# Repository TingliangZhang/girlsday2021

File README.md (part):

# Girl's Day of 2021 Presents Design
2021年交叉班女生节礼物——名片 设计

智能名片交互hhh

赛博朋克区块链

## 功能

Tagmo - 制作自己的Amiibo

[Popl - Your digital business card](https://popl.co/)

卡里面只有一个ID和我们服务器网址信息，具体这张名片能传达多少社交信息就由用户在网页端或者客户端配置了。以及最好加密一下，防止被轻易拿去干别的，比如友商出个教程，我们的卡就都变成他们的了

[The Blue Smart Card](https://blue.social/) - Reinventing the Name Tag. Create your virtual identity and be social again.

[Mobilo - The Smart Business Card](https://www.mobilocard.com/)

[Fuze Card, 0.84mm innovative electronic card technology.](https://fuzecard.com/)

KickStarter页面 [Fuze Card](https://www.indiegogo.com/projects/fuze-card-your-whole-wallet-in-one-card--3#/): Your Whole Wallet in One Card

[Unbox Therapy](https://www.youtube.com/channel/UCsTcErHg8oDvUnTzoqsYeNw)评测视频：[Your Whole Wallet In One Card](https://www.youtube.com/watch?v=7SPOVJi3H6g)

[Find Your Keys, Wallet & Phone with Tile's App and Bluetooth](https://www.thetileapp.com/en-us/)

[2.13寸 无源NFC 墨水屏 e-paper ESL电子货架标签 无线供电/刷新](https://item.taobao.com/item.htm?id=613699970326)

微雪NFC墨水屏标签

[小米碰碰贴2](https://item.jd.com/100014996634.html) nfc感应开关 全能投屏音乐接力碰触连网一碰连接米家智能场景

## 可参考项目

[PCB Business Card With NFC](https://www.instructables.com/PCB-Business-Card-With-NFC/) - 能存网址的名片

[THE NFC KEY](https://n-o-d-e.net/nfckey.html) - 存储密钥的带物理按键NFC

[Digital Business Card With NFC](https://www.instructables.com/Digital-Business-Card-With-NFC/) - 只是把NFCTag扔进两张纸之间去了。

[StyloCard](https://mitxela.com/projects/stylocard) - 乐器名片

[L-ink_Card](https://github.com/peng-zhihui/L-ink_Card) - 带墨水屏的NFC Tag

## 问题

手机的NFC功能可能默认关闭，而且NFC线圈位置不固定：苹果在正面顶部，安卓手机大多在背面。

## 进度追踪

2020/12 提出想法，女生节送智能名片

2021/1/27 开始设计

2021/1/28-29 元件选型和天线参数计算

2021/1/30-2/2 天线python脚本生成编写

2021/2/2 第一版测试板交付嘉立创打样，同时采购了元件，同时着手买NFC和RFID读取器

2021/2/4 V2交付打样，使用白色阻焊，尝试效果

2021/2/7 V1V2打样完成，焊接测试完成，功能完好

2021/2/8 开始规划网站服务，并学习React框架

2021/2/9 M24LR-discovery到货，验证了M24能用3.3V驱动STM32L系列单片机和一个液晶数位屏

2021/2/10 诚驰大哥加入，换用VUE框架，小菜鸡我同步开始学Vue

2021/2/11 除夕，依然干活，微雪的2.7inch NFC e-paper到货，测试尝试复现，并用电纸屏送上新年祝福

2021/2/12 大年初一，选取UX和UI设计工具，开始学习Figma

2021/2/13 开工画UX，画了一上午画出来一个登录界面，UX设计师真不容易，决定先用iPad的Procreate来画草图。

2021/2/15 用户体验设计碰头会，根据建议大改了交互流程，继续画了卡片管理界面，同时注册域名

2021/2/16 交给诚驰写网站，开始头大的Ruby和Jekyll开发环境配置

2021/2/17 搞网站备案，头大，Ruby和Jekyll开发环境还是没配好

2021/2/18 为了拿备案服务号，购买了阿里云一年的主机，并且配置Ubuntu环境和VS Code网页版，终于提交管局审核。把一大箱硬件开发的东西寄回清华。

2021/2/19 把Ruby和Jekyll开发环境配置好，其实就放弃了动态构建，只用build吧，研究Jekyll主题的使用

2021/2/20 返校，使用Ubuntu环境跑Jekyll

2021/2/21 - 22 组装服务器并给服务器装系统，走了很多弯路

2021/2/23 装好了Debian KDE 图形化系统，开始探索如何装虚拟化环境、网站部署

2021/2/24 开始部署Proxmox VE虚拟化服务，遇到了网关和DNS一系列问题

2021/2/25 两网站备案成功，但是服务器还是没跑起来，考虑回退回Debian Buster单系统，继续部署网站。

2021/2/26 开始第二个版本的PCB，准备采用黑色Silkskin，银色Paste，背面参考PCB尺子的设计。同时写社交模式。

2021年2月26日22点前后，人生中第一台自己搭出来的服务器和虚拟化子系统开始运行，快乐！

2021/2/27 确定正反面的形式，找到PCB Ruler参考

2021/2/28 传媒研究，定义碰一碰陌生人社交

2021/3/1 绘制V3样板

2021/3/2 交付打样，一共18个订单

2021/3/3 - 3/7 等待到货，同时在阿里云上部署服务，已部署主页和博客俩服务

2021/3/8 在女生节后一天，卡片到货了总共用了一周，嘉立创产能emmm。开始写文档梳理整件事情

2021/3/9 - 10 继续写

2021/3/11-12 要做发布会视频，24h速成blender

2021/3/13 焊芯片+做发布会PPT+建模

## To Do List

- [x] 云服务器配置
- [x] 本地服务器搭建（Dell R720）
- [x] 域名注册
- [x] 域名备案
- [x] SSL证书（上https）
- [x] 网站搭建
- [x] PCB外观设计
- [x] 自动生成PCB脚本编写（集成bitmap2component）
- [x] 硬件原理调试
- [x] UX和UI设计
- [x] 用户体验测试（大雾）
- [x] SD卡大小Tag设计和测试，特别是V槽拼版
- [ ] 加入墨水屏

## 工具

[KiCAD](http://www.kicad.org/)及其插件

[Interactive HTML BOM plugin for KiCad](https://github.com/openscopeproject/InteractiveHtmlBom)

[AutoCAD](https://www.autodesk.com/products/autocad/overview) 2021 Edu Edition

Linux下软件：

[Krita | Digital Painting. Creative Freedom.](https://krita.org/) 绘画软件

[Draw Freely | Inkscape](https://inkscape.org/) 矢量图编辑器

## 外形设计Outline

依据身份证等使用的ISO 7810-2003国际标准中的ID-1：ID-1的规定尺寸为85.60×53.98毫米（3.370×2.125英寸），常用于身份证、银行卡（如提款卡、信用卡）、驾照、个人名片，以及商店发出的忠实顾客卡等。其长宽比与黄金分割（1.618:1）接近。

ISO 7813规范ID-1塑胶银行卡的附加特性，包括0.76毫米厚度，及3.18毫米半径的圆角。

所以设计为

85.60×53.98毫米

3.18毫米半径的圆角

0.76毫米厚度（做0.8mmPCB板）

横向排版

或者用ID-3画成小的钥匙链

## Tile大小版本设计

Tile Pro：42mm x 42mm x 6.5mm  孔7mm直径

Tile Mate：35mm x 35mm x 6.2mm 孔6.5mm

初步设计为 40mm x 40mm x 1.6mm 孔6mm直径 倒角5mm直径圆

天线尺寸为30x30mm 0.3x0.3mm 11圈，电感4.98uH(@13.56Mhz)

天线封装焊盘为 0.3 x 0.5mm圆形通孔（嘉立创双面板最小过孔内径0.3mm,最小外径0.5mm）和 0.3 x 0.5mm矩形贴片焊盘

[嘉立创教学系列之：各软件拼板作业指引](http://club.szlcsc.com/article/details_468_1.html)

嘉立创拼版V割出货：走线和焊盘距板边距离≥0.4mm，否则可能涉及到板内的线路及焊盘，如果是拼版，则线离边必须要有0.4mm间距，否则v割会伤到线路。如果是单片出货，则需要帮≥0.2mm的间距。

VCUT(V割)板边离线的距离不小于0.4MM，CNC（锣边）正常是版边离线的距离不小于0.3MM，内槽离走线离线的最小距离不得小于0.3MM

V-CUT（V割工艺）：

（1）V割的拼板，板与板相连处不留间隙，也就是两块板外形线重叠放置，但是要注意，板子内的导线离V割线距离不小于0.4mm，以免切割时伤到走线。

（2）一般V割后残留的深度为1/3板厚，产品手动掰开后由于玻璃纤维丝有被拉松的现象，尺寸会略有超差，个别产品会偏大以上。

（3）V-CUT刀只能走直线，不能走曲线和折线。

（4）拼板尺寸在8cm以上才能做V-CUT工艺。

拼版设计：

可以考虑30cm x 30cm 九块边缘倒角板子拼起来，横排中间留2mm锣边，纵排无间距V割，纵排两侧有5mm工艺边和2.0mm定位孔及1.0mm的Mark点（一个焊盘）。

全部画在EdgeCut里面就好，嘉立创OEM会帮忙加V割或者锣边，如果版式一样，可以只画一个电路。在复制EdgeCut层的时候，可以在右边隐藏别的层。

由于强度问题，拼版V割的话还是要紧密连接，不能像上面这种设计。必须要加支撑才行。

但是拼版订单要多加钱。

所以还是先打单板吧。

## 简笔画头像生成

CV算法生成简笔画头像

[ArtLine](https://github.com/vijishmadhavan/ArtLine)

运行环境：[Colab](https://colab.research.google.com/github/vijishmadhavan/Light-Up/blob/master/ArtLine.ipynb)

CoLab中图片拖到根目录去上传，之后导入：

```python
img = PIL.Image.open("cai.jpg").convert("RGB")
```

[U-2-Net](https://github.com/NathanUA/U-2-Net)还有其前身[APDrawingGAN](https://github.com/yiranran/APDrawingGAN)

## 芯片选型

NXP NTAG

https://www.themobileknowledge.com/wp-content/uploads/2018/07/02-Webinar-slies-Antenna-design-for-NTAG-I2C-plus.pdf

ST25 Dynamic NFC Tags

https://www.st.com/en/nfc/st25-dynamic-nfc-tags.html

ST25DV04K

https://www.st.com/en/nfc/m24lr04e-r.html#overview

[M24LR04E-RMN6T/2](https://item.szlcsc.com/168717.html)[射频卡芯片](https://list.szlcsc.com/catalog/981.html)

测试板：

[M24LR-DISCOVERY](https://www.st.com/en/evaluation-tools/m24lr-discovery.html)

[X-NUCLEO-NFC02A1](https://www.st.com/en/ecosystems/x-nucleo-nfc02a1.html)

## NFC线圈设计

NFC Antenna Generator

https://kbeckmann.github.io/2016/06/19/NFC-Antenna-Generator/

[NFC Antenna Design | RF Design | eDesignSuite](https://eds.st.com/antenna/)

电路中天线电感计算计算：

主要参考AN2866 -  Antenna design procedure

Internal tuning capacitor in ST25DV04K SO8N(f = 13.56 MHz) $C_{TUN} = 28.5 pF$

计算公式：
$$
L_{A} C_{S} \omega^{2}=1
$$
具体推导：
$$
L_{A}=\frac{1}{4 \pi^{2} f^{2} C_{S}}
$$

$$
L_{A}=\frac{1}{4*3.14^{2}*13.56^{2}*28.5}=4.84uH
$$

谐振理论：

At low frequencies $\left(f<f_{\text {self res }} / 10\right),$ the stray capacitance $C_{\text {ant }}$ is negligible, $L_{A}=L_{\text {ant }}$ and the antenna reactance is given by $X_{A}=j L_{\text {ant }} \omega$.
At $13.56 \mathrm{MHz}, \mathrm{C}_{\text {ant }}$ value gets in the range of some $\mathrm{pF}$ and $\mathrm{L}_{\mathrm{A}}>\mathrm{L}_{\text {ant }}$.

The antenna impedance is $Z_{\text {ant }}=R_{A}+j L_{A} \omega$.

The NFC / RFID chip impedance is $Z_{S}=R_{s}+j / C_{S} \omega$.

For the equivalent RLC circuit, the total impedance is $Z_{\text {tot }}=Z_{\text {ant }}+Z_{s}$ and the resonant frequency is given by the condition $L_{A} C_{S} \omega^{2}=1$.
Optimum antenna tuning

At resonant frequency the total impedance reaches its minimum value $Z_{\text {tot }}=R_{A}+R_{S}$. The current in the antenna and the voltage delivered to the NFC / RFID chip are maximized, as the energy transferred to the device.

物理天线电感

嘉立创PCB成品外层铜厚1oz~2oz(35um~70um)选择35um

单片出货，走线和焊盘距板边距离≥0.2mm，否则可能涉及到板内的线路及焊盘。

直接留3.18mm边缘。

最小线隙，多层板3.5mil 单双面板5mil (1mil=1/1000inch=0.0254mm)

Antenna Length =  85.60 - 3.18x2 = 79.24 mm

Antenna Width = 53.98 - 3.18x2 = 47.62 mm

Turns = 6

Equivalent Inductance@13.56 Mhz = 4.98 µH

考虑到布线过程中的寄生电容等，接近4.84 µH，可以接受这一设计。

动态NFC天线计算主要参考 AN2972 How to design an antenna for dynamic NFC tags 

封装库画六圈螺线太难了，准备用dxf导入，先使用Adobe Illustrate绘制，依然太麻烦放弃。

还是写py脚本向导吧。

## NFC Antenna创建向导编写

参考官方示例

https://docs.kicad.org/5.1/en/pcbnew/pcbnew.html#Footprint_Wizards

[KiCad Scripting Examples](https://kicad.mmccoo.com/?page_id=83)

参考C:\Program Files\KiCad\share\kicad\scripting\plugins中的脚本。

C:\Users\Zhang\AppData\Roaming\kicad\scripting\plugins

[KiCad](https://github.com/KiCad)/**[kicad-footprint-wizards](https://github.com/KiCad/kicad-footprint-wizards)**

Defining Parameters

Footprint wizards are written in Python and are simple to develop. Each footprint wizard defines a number of footprint parameters, which are organised into categories called "Pages". [Read further on footprint parameters](https://github.com/KiCad/Footprint_Wizards/wiki/Footprint-Parameters)

主要参考microMatch_connectors.py，焊盘直接用SMD的长方形焊盘

To greatly simplify development of custom footprint wizards, the FootprintWizard base class is provided, and only a handful of simple functions need to be written for each wizards. [Read further on minimum wizard requirements](https://github.com/KiCad/Footprint_Wizards/wiki/Minimum-Wizard-Requirements)

先画一个最简单的练手

注意每次更改需要重启KiCAD新脚本才能生效，DeBug的时候因为这个浪费了不少时间。如果加载脚本失败，可以看到报错信息。

通过self.AddParam("Conductor", "spacing", self.uMM, 0.6)传递进来的 self.uMM 其实是已经转化成nm为单位的整型变量了，不需要再用pcbnew.FromMM(1.0)转换为nm。

算法可参考HTML的脚本，but我选择自己写hhh

二维数组需要初始化，测试py文件单独编写测试，VScode在安装Python插件后可以在Debug标签页查看变量。

之后手动添加焊盘，嘉立创双面板最小过孔内径0.3mm,最小外径0.5mm，一号焊盘用0.6x1.524mm矩形贴片，注意取消勾选F.Paste和F.Mask工艺层以令外观美观，二号焊盘用圆形通孔0.8x0.5mm，注意取消勾选F.Mask和B.Mask工艺层以令外观美观

左下角：（100，100）

右上角：（185.6，46.02）

中心定位点：（142.8，73.01）

## 信息填写

QR Code Wizard使用丝印层而非铜层

> Use SilkS layer: True
> Use Cu layer: False

字符：

最小字符：线宽6mil 字符高40mil，参数为极限值，尽量大于此参数

故字符采用0.2mm线宽 1mm字符高度

目前仅支持英文字符，KiCAD 6.0 将支持中文字符输入

## 矢量图导入

使用KiCAD主页 位图转换为元件 工具进行转换，直接可以导出kicad_mod文件，注意选择顶层丝印。

调黑白阈值还是很丑的，可以考虑通过Artline生成简笔画。

调整尺寸需要通过调分辨率实现，DPI越高图片越小。注意名片尺寸为85.60×53.98毫米，合适的头像应当为30mm x 30mm

同学们的头像参数调节

| Who      | DPI  | 尺寸      | 黑白阈值 |
| -------- | ---- | --------- | -------- |
| NFC Logo | 4000 | 10 x 10mm | 30       |
| cai      | 600  | 26 x 26mm | 80       |
| luna     | 700  | 30 x 30mm | 70       |
| danni    | 300  | 37.3      | 30       |

[Artistic PCB Design for Terrified Beginners](https://wiki.hope.net/index.php?title=Artistic_PCB_Design_for_Terrified_Beginners_workshop)

## NFC + 墨水屏

[实用新型] 一种无源NFC电子墨水屏显示系统 申请号：2020204091829

微雪e-Paper相关资料

https://www.waveshare.net/wiki/Main_Page#Display-e-Paper

特别是驱动板如[e-Paper Driver HAT](https://www.waveshare.net/wiki/E-Paper_Driver_HAT)等

但是屏线多数是SPI，所以估计需要一个STM32转接一下，其实之后的按键等外围设备也需要一个单片机来做。

NFC墨水屏模块

https://www.waveshare.net/wiki/2.7inch_NFC-Powered_e-Paper_Module

NFC烧写器开发板

https://www.waveshare.net/wiki/ST25R3911B_NFC_Board

购买了以上两种产品，发现NFC墨水屏的主控芯片型号竟然被磨掉了。。。

通过SWD接口接入，读取到型号是[STM32L4P5/Q5](https://www.st.com/en/microcontrollers-microprocessors/stm32l4p5-q5.html)，不出所料，ultra‐low‐power系列。

旁边的那个写着ofz 02f s20x的6pin芯片是 TPS62122，降压dcdc

NFC Tag估计是用STM32搞的，用NFC Tools Pro读取得到型号，是一个NXP MIFARE Ultralight

现在量一下电容充电曲线，7.5V，在识别和写图的时候充能，但是没有明显的充放电，应该就是个小电容。

## V1V2焊接调试

注意ST24的marker是一边的斜边对应1号脚所在的位置，其实反色的ST标着对应的也是marker。

在不带载的情况下，EH输出大约为0.5V以下。暂时不上LED了，LED允许电压普遍在2.5V 20mA左右，可能会BOOM。下个版本加电阻吧。

## V3名片设计

增加LED限流电阻

在背面增加两个具有代表性的SMD芯片封装，贴片装饰LQFP-100和BGA-1mm-256

删除头像丝印，规范个人信息排版方式

删除中心定位焊盘

### V3.0 被抛弃的花里胡哨的PCB信仰尺风格设计

背面参考PCB尺子的设计

最典型的就是NVIDIA的尺子，但是可能找不到源文件，只能找类似的参考。

嘉立创PCB

https://lceda.cn/OSHWHubkai-yuan-ying-jian/li-chuangeda-chi-zi

Github and KiCAD

[PCBruler Github Repo](https://github.com/jbtronics/PCBruler)  [PCBrulerS Project Intro](https://hackaday.io/project/25482-pcbrulers) 准备主要参考这一个

[PCB Business Card Ruler With QR and NFC](https://www.instructables.com/PCB-Business-Card-Ruler-With-QR-and-NFC/)

Eagle 开源

[Adafruit-PCB-Ruler](https://github.com/adafruit/Adafruit-PCB-Ruler)

[SparkFun_PCB_Ruler](https://github.com/sparkfun/SparkFun_PCB_Ruler)

放张图纪念一下一晚上的工作

### V3.1版本 简约风设计

考虑电路在背面，个人信息在正面。

背面增加未来交互Logo，在铜层，加阻焊，闪闪发光其实不好看

25mm x 25mm 大小

有一个问题，Logo存在闭合曲线部分，可能电磁感应会有问题，特别是有一部分特别细，有冒烟隐患。

需要更改文件，切断最细部分的连线。由于没有Ai，我用画图3D加上了两个白色的直角三角形，从而断开了回路。

同时删除中心定位焊盘，加入辅助轴原点。

名片正面信息：

姓名

个人标签，如：

交互设计师，用户体验工程师，网页前端架构师，艺术家，嵌入式工程师

美术农民工，影视包工头，码农，极客

头像：30x30mm大小，线宽至少0.2mm

缩放按照1500DPI来，线宽能达到0.3mm，34.7mm正方形，有点大，得调整位置。

身份信息：

Tsinghua University

Info Art Design

Interdisciplinary Project ?

UID?

二维码决定先不做定制化，统一写为interact.cool网址，即跳转到网站登录或APP下载页面，登陆后双方互扫UID码即可。

Designed by Tingliang, Copyright © 2021 Tingliang Zhang CC BY-NC-ND

## V4钥匙链设计

缩小钥匙孔、线圈、整个的尺寸，到30x30cm，以便一个10x10的上面能打9个。

在正面印上未来交互的图案，背面印上二维码。和部分装饰性丝印，比如LQFP-64和BGA-100

天线重新生成一下：0.3mm线宽、0.2mm间距、25*25mm、13圈的线圈，自感4.97uH，接近4.84uH

0.8mm板厚，选择白色或黑色阻焊，3x3V-Cut拼板

## 服务器搭建

服务器选型

Dell R720 2U刀片服务器 3.5寸盘架x8  双路至强E5-2678V2 20核40线程处理器 16G内存 H710阵列卡 3T储存空间（后续可扩容） 750W电源 100Mbps带宽 公网IP

最好带有DELL IDRAC7 企业版授权

BUT 校内1024以下端口不开，而且会被学校查水表，不让校内建站。所以可能还是学生机更好。。。

使用阿里云学生机吧。。。

三丰云可以免费用，但是只用作测试，不能用为生产环境，因为每五天需要点一次延期，太过分了。

[PowerEdge R720](https://www.dell.com/support/home/zh-cn/product-support/product/poweredge-r720/overview)

服务编号(Service Tag)：C8L4Z42

操作系统选择Debian+KVM(Ubuntu+WinServer)

插上E5-2680v2，内存条，开机

第一次开机先清一下H710的默认值，可能之前的设置不对。

重启后按F2进入System Config，最后发现是盘没插好，2.5寸用3.5寸盘架还是有点问题，换成3.5寸就好了

F2-System Setup - Device Settings - H710 Raid setting - Create new virtual disk - Save and restart   就可以成功挂在硬盘到阵列卡上面了，当有 1 Virtual Device 的时候就说明成了。

但是又识别不到U盘了，可能是因为有阵列卡？也可能没断电插拔？重新烧写后按F10-BOOT setting 选择USB设备启动。

注意Debian Live KDE的安装界面锁屏默认密码为Live

总结：首先F2-System Setting - Device Setting - H710 - Create new virtual disk - Initialize - Fast Initialize 

替代办法：https://jingyan.baidu.com/article/4b52d702b7d396fc5d774b49.html 直接ctrl + R进入Raid设置

在BIOS Setting 确认SATA setting是Raid

重启，没有直接引导，需要按F11选择C：-- USB 启动即可

安装的时候BUG无法分区...搜了一下，是因为2T+硬盘要切换成UEFI

[Dell R720上的系统安装问题的解决办法](https://www.cnblogs.com/wgp13x/p/3750957.html)

可以使用[Microsoft Windows and Office ISO Download Tool](https://www.heidoc.net/joomla/technology-science/microsoft/67-microsoft-windows-and-office-iso-download-tool)下载Windows系统，但是好像没有Windows Server 2019

先安Debian：[Debian 64 位 PC（amd64）的安装手册](https://www.debian.org/releases/stable/amd64/)

去tuna下载[Debian 10.8.0 (amd64, DVD installer (Part 1))](https://mirrors.tuna.tsinghua.edu.cn/debian-cd/current/amd64/iso-dvd/debian-10.8.0-amd64-DVD-1.iso)

先安Ubuntu吧qwq

[Installation instructions for Ubuntu Server ](https://ubuntu.com/tutorials/tutorial-install-ubuntu-server)

按照[Create a bootable USB stick on Windows](https://ubuntu.com/tutorials/create-a-usb-stick-on-windows)使用[Rufus](https://rufus.ie/)烧写U盘

最后还是决定用Debian了。。。在Debian里在搞虚拟化主机KVM安Windows之类的

TFTP网络配置需要认真看看。

操作系统选择方面，先使用VirtualBox尝试安装，比如Debian Live之类的。

Debian的各种桌面环境参考：https://www.eet-china.com/mp/a10976.html

[Debian 10.8.0 (amd64, Live CD with gnome and non-free firmware)](https://mirrors.tuna.tsinghua.edu.cn/debian-nonfree/images-including-firmware/current-live/amd64/iso-hybrid/debian-live-10.8.0-amd64-gnome+nonfree.iso)

总结如下：

1. 建立Raid
- 开机，按ctrl+R进行Raid配置
- 选择Raid卡，按F2，清除现有Raid
- 光标选择到Raid卡，按F2，create new VD，将6个HD全做Raid5（或Raid6）
- 按F2，init VD （初始化VD）
- 配置完成后重启
2. 开机按F2进行BIOS设置 （如果总硬盘小于2T此步略去）进入BIOS，将启动模式选择成UEFI
3. 开机按F11进行UEFI启动（如果总硬盘小于2T此步略去）
4. 进入Boot Manager，选择UEFI Boot Menu（如果总硬盘小于2T，选择Bios Boot Menu）
5. 选光驱（插入系统盘）
6. Press any key to install OS

后续高分屏问题解决：尝试使用Quadro K2200专业卡，使用DP输出，但是后面板挡住了DP线，需要一个扁平一点的DP。

服务器后台运行在后面加 & 即可

如果有输出，ssh断开后程序也可能会停止运行，所以在前面加上 nohup

Debian10第一次安装ssh：

```bash
sudo apt-get install ssh
sudo systemctl restart ssh
```

之后可以配置公钥

## 域名备案相关

总的来说：麻烦到爆炸

在购买域名的代理商处进行域名实名认证，在购买云服务器的运营商拿备案服务号，并走备案网站流程。

首先域名实名认证，三天后同步到管局，进行网站备案

在阿里[备案入口](https://beian.aliyun.com/)上传一大堆资料和无数次验证码之后，提交初审，一个工作日后会给你打电话确认，把你的资料改一遍，个人申请不能涉及团队，之后提交管局。

工信部会给你发个短信再次查验身份。

阿里云管局审核最快也得一周以后，基本上通过都是两周以后

备案成功后，会给你的手机，邮箱发送一个备案密码，以及备案号，备案密码一定要好好保管，备案密码是以后变更备案信息的重要依据。

我今天（2021年2月18日）提交的管局审核，女生节前希望能批下来。

## 阿里云服务器相关

纠结好久，最后选择购买阿里云的[轻量应用服务器](https://www.aliyun.com/product/swas)，首先有学生价，其次可以安装Ubuntu，比腾讯云的轻量应用服务器要好。

最主要的是，[网站备案](https://beian.aliyun.com/)需要的[备案服务号](https://help.aliyun.com/document_detail/36938.html)轻量应用服务器实例可以提供5个（参见[支持备案的云服务及备案网站数量](https://help.aliyun.com/document_detail/36891.html)）

我选择安装Ubuntu20.04，进去之后好快啊，通过输入“sudo su root”切换至root账号

可选[用VNC搭建Ubuntu VNC可视化界面](https://help.aliyun.com/knowledge_detail/59330.html)

vnc4server还没出Ubuntu20.04版本的，啊这。。。

我还是用[code-server](https://github.com/cdr/code-server)吧。

### Code-Server安装

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
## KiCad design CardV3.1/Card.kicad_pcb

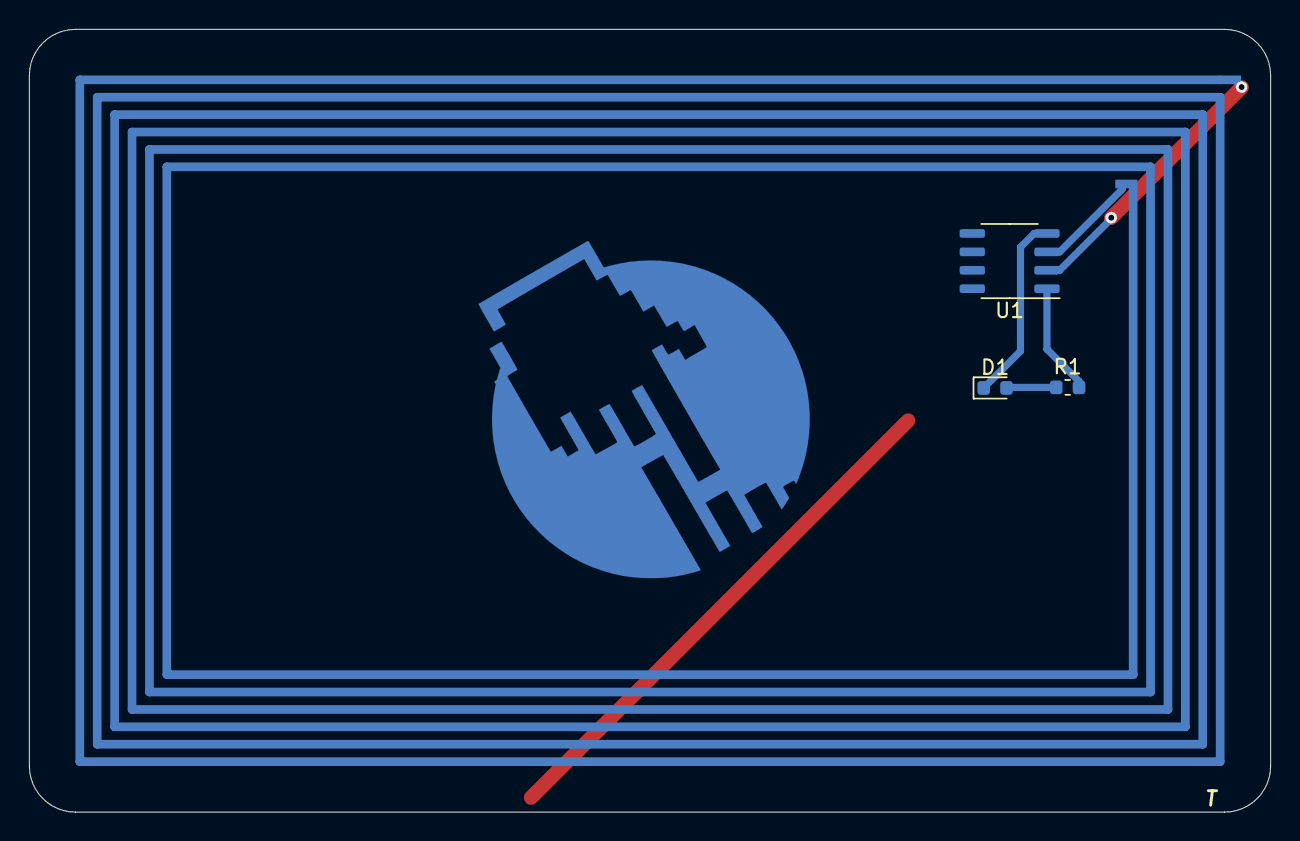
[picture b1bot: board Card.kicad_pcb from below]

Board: 2 copper layers, 85.6 x 54.0 mm, 5 parts (4 on the bottom side), 5 nets.

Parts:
AE1: Antenna_Loop; NFC-Antenna_6_79.24x47.62_0.6x0.6mm
D1: LED; LED_0603_1608Metric
QR: https://interact.cool/; interact.cool
R1: R; R_0603_1608Metric
U1: M24LR04E-R; SO-8_3.9x4.9mm_P1.27mm

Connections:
+3V3: R1.2, U1.1
GND: D1.1, U1.4
unnamed: AE1.1, U1.3
unnamed: AE1.2, U1.2
unnamed: D1.2, R1.1

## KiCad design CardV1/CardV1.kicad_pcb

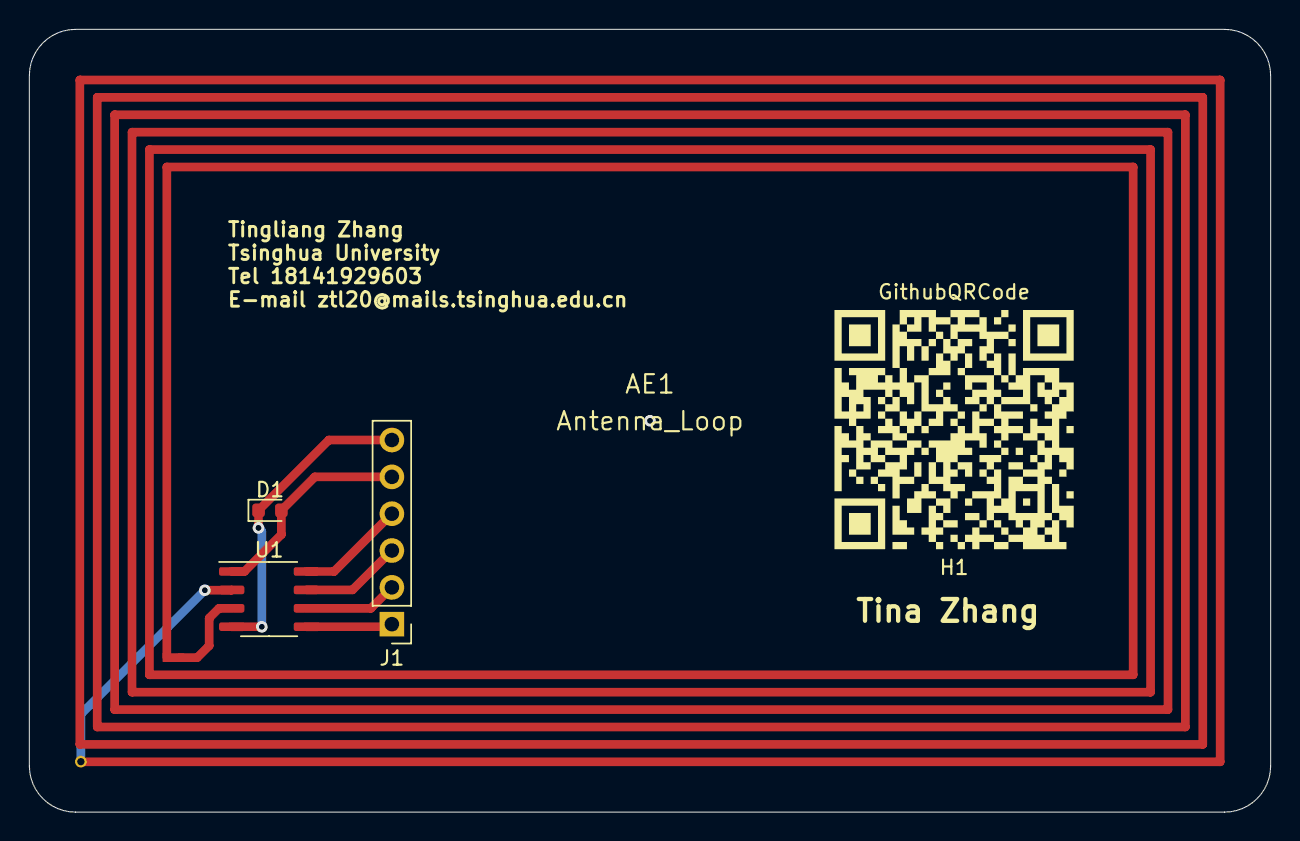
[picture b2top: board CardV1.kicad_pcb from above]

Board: 2 copper layers, 85.6 x 54.0 mm, 5 parts (0 on the bottom side), 8 nets.

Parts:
AE1: Antenna_Loop; NFC-Antenna_6_79.24x47.62_0.6x0.6mm
D1: LED; LED_0603_1608Metric
H1: GithubQRCode; tingliangzhang-github-io
J1: Conn_01x06_Male; PinHeader_1x06_P2.54mm_Vertical
U1: M24LR04E-R; SO-8_3.9x4.9mm_P1.27mm

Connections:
+5V: D1.2, J1.5, U1.1
GND: D1.1, J1.6, U1.4
unnamed: AE1.1, U1.3
unnamed: AE1.2, U1.2
unnamed: J1.1, U1.5
unnamed: J1.2, U1.6
unnamed: J1.3, U1.7
unnamed: J1.4, U1.8

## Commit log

2021-01-30 Outline
2021-01-30 ArtLine ipynb
2021-01-30 使用本地照片
2021-01-31 Datasheet
2021-01-31 Hole
2021-01-31 4.84uH
2021-01-31 Begin Antenna Drawing
2021-02-01 nfc-antenna-generator HTML
2021-02-01 Update NFCAntenna.py
    终于能画出线啦
2021-02-01 Finish NFC script
2021-02-01 VScode Debug
2021-02-02 Almost Finish
2021-02-02 Avatar
2021-02-02 V1打样
2021-02-02 Tile大小版本设计
2021-02-02 CardV2
2021-02-02 Create fp-lib-table
2021-02-02 ST25 lib
2021-02-03 Almost Finish V2
2021-02-03 Logo
2021-02-03 失败的拼版
2021-02-03 拼板总结
2021-02-03 拼板完成
2021-02-03 改为单板
2021-02-07 V1和V2调试
2021-02-11 NFC 墨水屏 测试
2021-02-12 V3 Update
2021-02-16 Jekyll install
2021-02-18 ali yun server
2021-02-18 Code Server
2021-02-18 备案总结
2021-02-18 安Ubuntu虚拟机
2021-02-19 Jekyll成功运行
2021-02-21 先试试Debian 10.8.0 (amd64, Live CD with gnome and non-free firmware)
2021-02-22 Finally success boot
2021-02-23 装服务器总结
2021-02-23 KVM begin
2021-02-23 ProxmoxVE
2021-02-23 在Debian之上安装PVE
2021-02-24 R720上Proxmox的问题
2021-02-26 Nano Pi
2021-02-26 R720上Proxmox的问题solve
2021-02-26 Success proxmox VE
2021-02-26 DNS error solve
2021-02-26 debian9 DNS
2021-02-26 mount ssd
2021-02-26 cao!
2021-02-26 上传iso的大坑
2021-02-26 Success PVE!
2021-02-26 remarkable
2021-02-28 move bp to this repo
2021-02-28 change name
2021-03-01 Import PCB Ruler Lib
2021-03-01 我枯了，大家觉得这一版本不好看，改
2021-03-01 V3.2 ini
2021-03-01 V3.1
2021-03-01 Finish 3.1 ?
2021-03-02 FutureInteraction
2021-03-02 Add Interaction LOGO
2021-03-02 断掉LOGO回路
2021-03-02 批量产出
2021-03-06 Blog ini
2021-03-06 Update Gemfile
2021-03-06 add Minimal Mistakes
2021-03-06 add posts and pages
2021-03-06 archive
2021-03-07 Future Interaction
2021-03-08 All copy
2021-03-08 V4 ini
2021-03-08 Finish and Print V4
2021-03-09 HomeDesignFromDreamweaverTemplate
2021-03-09 index.html
2021-03-09 nginx config
2021-03-14 Swiss
2021-03-14 del swiss
2021-03-16 MOMO
2021-03-18 0318
2021-03-19 arrange account
2021-03-26 cite wiki:Ingress
2021-03-26 cite debug
2021-03-26 Hardware tex
2021-03-26 Short BP Arrange
2021-03-26 BusinessPlanShort
2021-03-28 Template Xelatex
2021-03-28 Add Lots of Software Fig
2021-03-28 Software
2021-03-28 Ingress
2021-03-28 Hardware
